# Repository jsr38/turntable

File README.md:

# turntable
3D scanning turntable

This repository contains hardware designs and firmware to enable a 3D scanning turntable to be constructed.

The turntable operates with either a mains AC motor with feedback or a DC motor.  In both cases a rotary optical encoder is employed to give accurate feedback of current position to upper software layers.

In my fork of the [bqlabs/horus](https://github.com/jsr38/horus) repository you can find my modifications to the bqlabs/horus scanning software which allow either a pair of laser line emitters and RGB camera or a Microsoft Kinect V2 aka Kinect One which contains an IR depth sensor and RGB camera, allowing full colour but lower resolution scans under Linux or Mac OS X.

The turntable electronics are designed to interface to an Arduino Uno as a pair of expansion shields.

opto-interface:

opto-interface prototype:

* [first movements](https://youtu.be/DPcl0FW12F8)

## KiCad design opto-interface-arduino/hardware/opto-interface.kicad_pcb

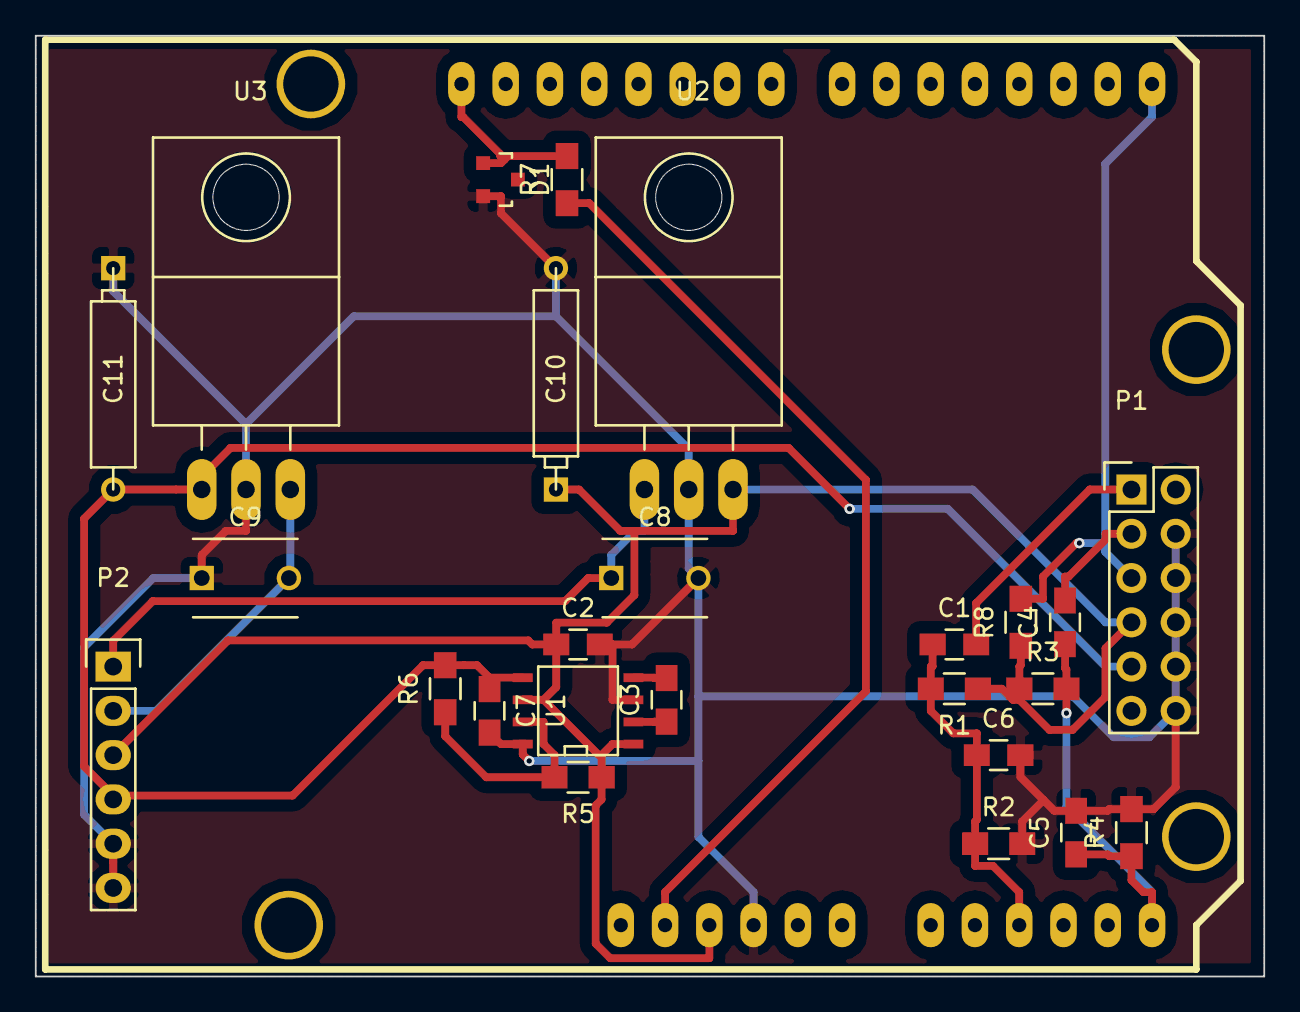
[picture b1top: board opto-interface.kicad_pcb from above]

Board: 2 copper layers, 70.5 x 54.0 mm, 26 parts (0 on the bottom side), 15 nets.

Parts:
C1, C2, C4, C7: 10uF; C_0805_HandSoldering
C3: 2u2F; C_0805_HandSoldering
C5, C6: 1nF; C_0805_HandSoldering
C8, C9: 0u1F; C_Disc_D6_P5
C10, C11: 2u2F; CP5
D1: ZENER; SOT-23
P1: CONN_02X06; Pin_Header_Straight_2x06
P2: CONN_01X06; Pin_Header_Straight_1x06
R1, R2, R3, R4, R5, R6: 100kR; R_0805_HandSoldering
R7: 1k3R; R_0805_HandSoldering
R8: 390R; R_0805_HandSoldering
SHIELD1: ARDUINO_SHIELD; ARDUINO SHIELD
U1: max889; SOIC-8-N
U2: LM7805; TO-220_regul_Horizontal_LargePads
U3: LM7905; TO-220_regul_Horizontal_LargePads

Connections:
+3V3: R7.1, SHIELD1.3V3
+5V: C2.1, C10.1, P1.7, P2.3, R1.1, R3.1, R5.1, R8.1, SHIELD1.5V, U1.1, U1.6, U2.VO
+12V: C8.1, P2.1, U2.VI
-5V: C7.1, C11.2, P1.9, P2.4, R6.2, U1.5, U3.VI
-12V: C9.2, P2.2, U3.VO
GND: C2.2, C5.2, C6.2, C7.2, C8.2, C9.1, C10.2, C11.1, D1.2, P1.4, P1.6, P1.8, P1.10, P1.12, P2.5, P2.6, R2.2, R4.2, SHIELD1.GND1, U1.3, U1.8, U2.GND, U3.GND
unnamed: C1.1, C6.1, R1.2, R2.1, SHIELD1.AD2
unnamed: C1.2, P1.1
unnamed: C3.1, U1.2
unnamed: C3.2, U1.4
unnamed: C4.1, C5.1, R3.2, R4.1, SHIELD1.AD5
unnamed: C4.2, P1.3
unnamed: D1.1, R7.2, SHIELD1.AREF
unnamed: P1.5, R8.2, SHIELD1.0
unnamed: R5.2, R6.1, U1.7

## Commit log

2016-01-16 Add jsr38/equipment as submodule
2016-01-16 Datasheet and web pages for Canon K-1 optical rotary encoder
2016-01-18 Initial commit of tripod QR plate
2016-01-18 Modify to suit Velbon Sherpa 250 tripod with PH-157Q head.
2016-01-18 Add QR plate STL file
2016-01-18 Add Atmel ATmega328P datasheet
2016-01-18 Intial commit of PCB and Arduion sketch for controller.
2016-01-20 Remove spurious scad file...
2016-01-20 Try again :\(
2016-01-25 Tidy up, rename .ino to something valid ;) Update to latest QR mount plate design.
2016-01-25 Make Arduino happy :(
2016-01-25 Add Arduino shield component and PCB files. Begin schematic capture.
2016-01-27 Move current Kicad files to hardware subdirectory. Update tripod QR plate to be slightly less wide.
2016-01-27 Update relative path to libraries. Export netlist.
2016-01-27 Add library papers and do initial Arduino Shield board layout.
2016-01-29 Add AD1580 datasheet.
2016-01-31 Move encoder primer to github
2016-02-06 Update to include external power connector.
2016-02-11 Add notes on -ve supply generation
2016-02-11 Add charge pump data sheet MAX889
2016-03-03 Relocate opto-encoder documentation to library/
2016-03-04 Add charge pump for -ve supply and skeleton input filter. Add calculations document.
2016-03-04 Add spice schematic for ADC front-end sim.
2016-03-07 Start firmware. Add serial and gocde parser from Grbl. Update simulations of LP filter and level shifter for ADC frontend.
2016-03-13 AC sweep 10Hz - 120kHz (Bode plot)
2016-05-31 Add filter simulations, first pass layout, some calculations and some skeleton code.
2016-06-11 Complete v 0.1 layout
2016-06-22 Add image to README.md
2016-07-05 Add borniers kicad library. Add polarization based 3d scan paper, references and book chapter on optical-material interactions.
2016-07-20 Modify layout to ahem follow the datasheet guidance on MAX889. Update analogue input schematic for simulation to accomodate steeper low-pass roll-off.
2016-07-20 Update 3D image
2016-07-24 Add photo of prototype opto interface to README.md
2016-07-24 Update README.md with video of first movements
